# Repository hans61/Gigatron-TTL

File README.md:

# Gigatron-TTL - extensions and components

## In Circuit EPROM emulator and debugger
my assembly experiences with the project from  gesari (Jesus Arias)

https://github.com/hans61/Gigatron-TTL/tree/main/InCircuitEPROMemulator

## Pluggy-Reloaded
A Pluggy Reloaded with the Arduino Nano Every.

## FreeCAD
My useful things for the 3d printer.

## 8Bit-audio
Attempt of audio output with a DAC TLC7524 at the external extension of lb3361.

## Video-Repeater
A pcb for the video repeater from Axelb.

## sound card
Sound card with sn76489 (in progress)

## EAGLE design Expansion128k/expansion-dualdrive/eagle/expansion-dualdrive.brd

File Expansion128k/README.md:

# Gigatron Extension 128k+

The 128k+ extension provides 128 kbyte RAM and an SPI interface for the Gigatron.
The first draft was discussed here: https://forum.gigatron.io/viewtopic.php?f=4&t=64

Another extension is lb3361's expansion-retro https://github.com/lb3361/gigatron-lb/tree/main/extension-retro.
It uses two GAL and extends the original with additional I/O functions. The GAL also allows changes to the function through GAL programming.

For all those who don't want GALs and for the new "dev128k7.rom" from lb3361 I made a new PCB from Marcel's original. The extension includes all the latest changes and pin header for two SD card breakout.

In the end there were two PCBs because an old problem reappeared while testing the first one. DANGER! the original circuit does not work with two SD cards and the current ROMs.
This is partly due to the SD cards, which only behave like SPI devices after they have been switched to this mode. The second problem is the SD breakout boards used, which permanently put the MISO signal on the output, independent of /CS. In the original circuit, the MISO signals are separated by the hardware, but they are combined again in the ROM
("anda(0b00001111) #28+i*12 This is why R1 as pull-DOWN is simpler").

One way to solve the problem is to modify the breakout, which requires some skill.

The second possibility is to solve it with hardware. I did that with the second PCB. I borrowed two gates from the 74125 for the solution. This reduces the available SPI on this PCB from 4 to 2.

I built and tested both PCBs. They work as expected.

## original

## dualdrive modify

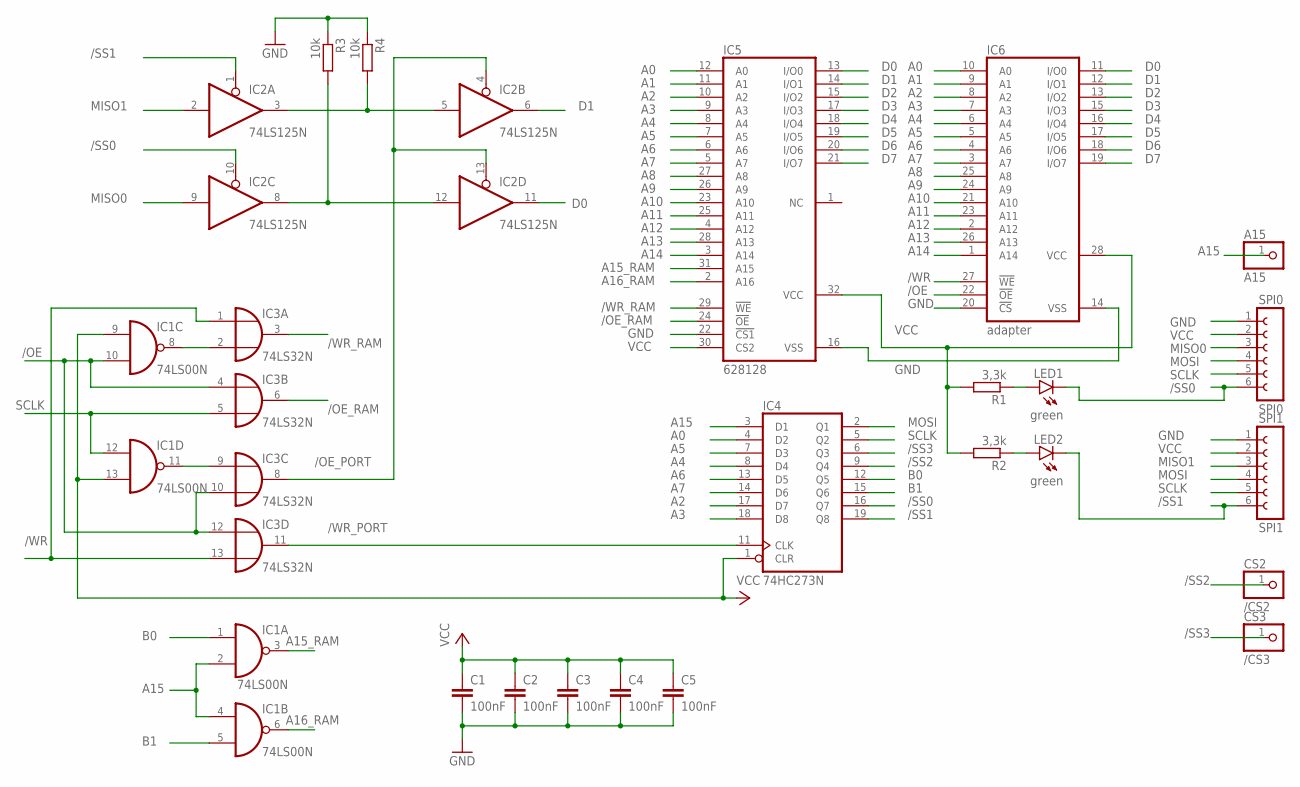
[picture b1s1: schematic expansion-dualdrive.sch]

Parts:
A15: A15; 1X01
C1, C2, C3, C4, C5: 100nF; C050-024X044
CS2: /CS2; 1X01
CS3: /CS3; 1X01
IC1: 74LS00N; DIL14
IC2: 74LS125N; DIL14
IC3: 74LS32N; DIL14
IC4: 74HC273N; DIL20
IC5: 628128; DIL32
IC6: adapter; DIL28-6
LED1, LED2: green; LED3MM
R1, R2: 3,3k; 0207/10
R3, R4: 10k; 0207/10
SPI0: SPI0; FE06
SPI1: SPI1; FE06

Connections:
/OE: IC1.10 (I1), IC3.4 (I0), IC3.10 (I1), IC3.12 (I0), IC6.22 (!OE)
/OE_PORT: IC2.4 (OE), IC2.13 (OE), IC3.8 (O)
/OE_RAM: IC3.6 (O), IC5.24 (!OE)
/SS0: IC2.10 (OE), IC4.16 (Q7), LED1.K (C), SPI0.6
/SS1: IC2.1 (OE), IC4.19 (Q8), LED2.K (C), SPI1.6
/SS2: CS2.1, IC4.9 (Q4)
/SS3: CS3.1, IC4.6 (Q3)
/WR: IC3.1 (I0), IC3.13 (I1), IC6.27 (!WE)
/WR_PORT: IC3.11 (O), IC4.11 (CLK)
/WR_RAM: IC3.3 (O), IC5.29 (!WE)
A0: IC4.4 (D2), IC5.12 (A0), IC6.10 (A0)
A1: IC5.11 (A1), IC6.9 (A1)
A2: IC4.17 (D7), IC5.10 (A2), IC6.8 (A2)
A3: IC4.18 (D8), IC5.9 (A3), IC6.7 (A3)
A4: IC4.8 (D4), IC5.8 (A4), IC6.6 (A4)
A5: IC4.7 (D3), IC5.7 (A5), IC6.5 (A5)
A6: IC4.13 (D5), IC5.6 (A6), IC6.4 (A6)
A7: IC4.14 (D6), IC5.5 (A7), IC6.3 (A7)
A8: IC5.27 (A8), IC6.25 (A8)
A9: IC5.26 (A9), IC6.24 (A9)
A10: IC5.23 (A10), IC6.21 (A10)
A11: IC5.25 (A11), IC6.23 (A11)
A12: IC5.4 (A12), IC6.2 (A12)
A13: IC5.28 (A13), IC6.26 (A13)
A14: IC5.3 (A14), IC6.1 (A14)
A15: A15.1, IC1.2 (I1), IC1.4 (I0), IC4.3 (D1)
A15_RAM: IC1.3 (O), IC5.31 (A15)
A16_RAM: IC1.6 (O), IC5.2 (A16)
B0: IC1.1 (I0), IC4.12 (Q5)
B1: IC1.5 (I1), IC4.15 (Q6)
D0: IC2.11 (O), IC5.13 (I/O0), IC6.11 (I/O0)
D1: IC2.6 (O), IC5.14 (I/O1), IC6.12 (I/O1)
D2: IC5.15 (I/O2), IC6.13 (I/O2)
D3: IC5.17 (I/O3), IC6.15 (I/O3)
D4: IC5.18 (I/O4), IC6.16 (I/O4)
D5: IC5.19 (I/O5), IC6.17 (I/O5)
D6: IC5.20 (I/O6), IC6.18 (I/O6)
D7: IC5.21 (I/O7), IC6.19 (I/O7)
GND: C1.2, C2.2, C3.2, C4.2, C5.2, IC1.7 (GND), IC2.7 (GND), IC3.7 (GND), IC4.10 (GND), IC5.16 (VSS), IC5.22 (!CS1), IC6.14 (VSS), IC6.20 (!CS), R3.1, R4.1, SPI0.1, SPI1.1
MI0: IC2.8 (O), IC2.12 (I), R3.2
MI1: IC2.3 (O), IC2.5 (I), R4.2
MISO0: IC2.9 (I), SPI0.3
MISO1: IC2.2 (I), SPI1.3
MOSI: IC4.2 (Q1), SPI0.4, SPI1.4
unnamed: IC1.8 (O), IC3.2 (I1)
unnamed: LED1.A, R1.1
unnamed: IC1.11 (O), IC3.9 (I0)
unnamed: LED2.A, R2.1
SCLK: IC1.12 (I0), IC3.5 (I1), IC4.5 (Q2), SPI0.5, SPI1.5
VCC: C1.1, C2.1, C3.1, C4.1, C5.1, IC1.9 (I0), IC1.13 (I1), IC1.14 (VCC), IC2.14 (VCC), IC3.14 (VCC), IC4.1 (CLR), IC4.20 (VCC), IC5.30 (CS2), IC5.32 (VCC), IC6.28 (VCC), R1.2, R2.2, SPI0.2, SPI1.2

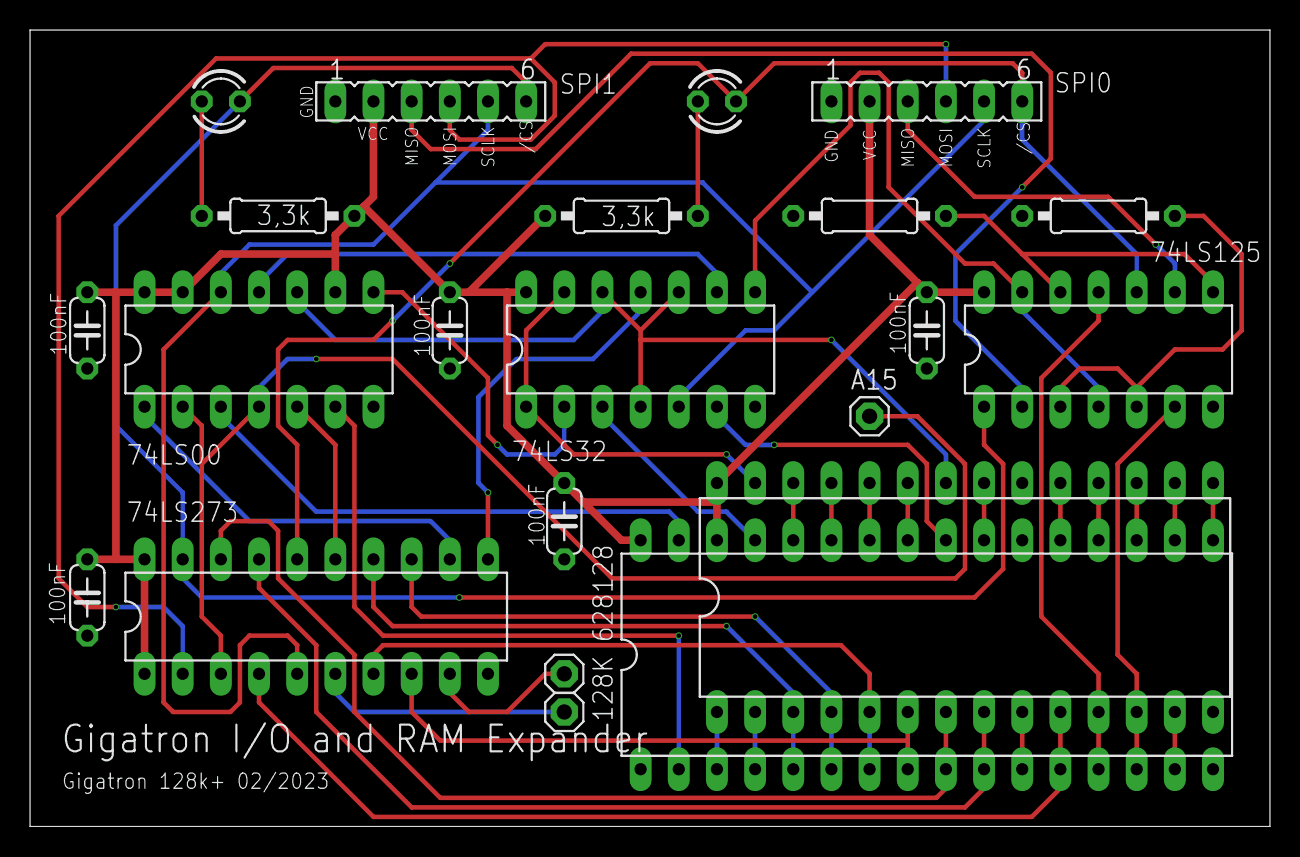
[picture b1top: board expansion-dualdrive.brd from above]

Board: 2 copper layers, 82.5 x 53.0 mm, 22 parts (0 on the bottom side), 50 nets.

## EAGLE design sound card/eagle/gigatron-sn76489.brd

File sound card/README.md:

# sound card with sn76489
I accidentally stumbled across the sound chip sn76489. Since it can only be controlled via outputs, it is well suited for the extension-retro of lb3361.
This is my attempt for a Gigatron sound card (Rev.3 still in work).

Unfortunately, I haven't had any success so far in producing a reasonable sound on the board. Now I have finally discovered the cause of the problem.
The SN76489 is available in two different pinouts. The difference is mirrored data pins.

| SN76489  Pin  | Pinout 1 | Pinout 2 |
|:-------:|:--------:|:--------:|
|    3    |    D0    |    D7    |
|    2    |    D1    |    D6    |
|    1    |    D2    |    D5    |
|   15    |    D3    |    D4    |
|   13    |    D4    |    D3    |
|   12    |    D5    |    D2    |
|   11    |    D6    |    D1    |
|   10    |    D7    |    D0    |

Pinout 1:
https://map.grauw.nl/resources/sound/texas_instruments_sn76489an.pdf

Pinout 2:
https://en.m.wikipedia.org/wiki/Texas_Instruments_SN76489

I solved the problem on the breadboard for now.

I'm still testing a small adapter board. When she leaves I will post it here.
I will also rework the PCB itself.

First tests (fast cell phone video):
https://www.youtube.com/watch?v=wv5x-WD0vzI

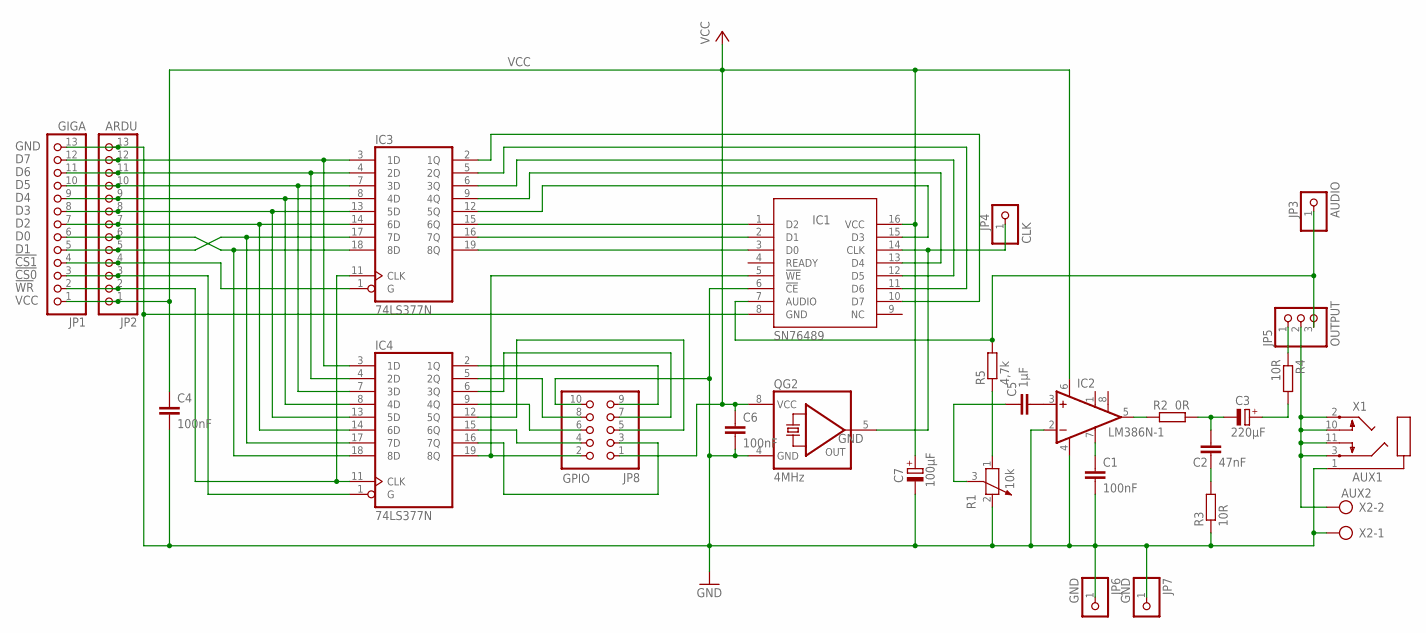
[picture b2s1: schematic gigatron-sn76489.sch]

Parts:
C1, C4, C6: 100nF; C050-025X075
C2: 47nF; C050-025X075
C3: 220µF; E2,5-7
C5: 1µF; C050-025X075
C7: 100µF; E2,5-7
IC1: SN76489; ALEX-PARTS_DIL16
IC2: LM386N-1; DIL08
IC3, IC4: 74LS377N; DIL20
JP1: GIGA; 1X13/90
JP2: ARDU; 1X13
JP3: AUDIO; 1X01
JP4: CLK; 1X01
JP5: OUTPUT; 1X03
JP6, JP7: GND; 1X01
JP8: GPIO; 2X05
QG2: 4MHz; DIL08S
R1: 10k; PT-10S
R2: 0R; 0207/10
R3, R4: 10R; 0207/10
R5: 4,7k; 0207/10
X1: AUX1; SJ1-352XN
X2: AUX2; AK500/2

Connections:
!CS0: IC4.1 (G), JP1.3, JP2.3
!CS1: IC3.1 (G), JP1.4, JP2.4
!SWR: IC1.5 (!WE), IC4.19 (8Q), JP8.2
!WR: IC3.11 (CLK), IC4.11 (CLK), JP1.2, JP2.2
AUXOUT: JP5.2, X1.2, X1.3, X1.10, X1.11, X2.2
CLK4MHZ: IC1.14 (CLK), JP4.1, QG2.5 (OUT)
D0: IC3.18 (8D), IC4.18 (8D), JP1.6, JP2.6
D1: IC3.17 (7D), IC4.17 (7D), JP1.5, JP2.5
D2: IC3.14 (6D), IC4.14 (6D), JP1.7, JP2.7
D3: IC3.13 (5D), IC4.13 (5D), JP1.8, JP2.8
D4: IC3.8 (4D), IC4.8 (4D), JP1.9, JP2.9
D5: IC3.7 (3D), IC4.7 (3D), JP1.10, JP2.10
D6: IC3.4 (2D), IC4.4 (2D), JP1.11, JP2.11
D7: IC3.3 (1D), IC4.3 (1D), JP1.12, JP2.12
GND: C1.2, C4.2, C6.2, C7.-, IC1.6 (!CE), IC1.8 (GND), IC2.2 (-IN), IC2.4 (GND), IC3.10 (GND), IC4.10 (GND), JP1.13, JP2.13, JP6.1, JP7.1, JP8.10, QG2.4 (GND), R1.2, R3.1, X1.1, X2.1
LM5: IC2.5 (OUT), R2.1
LM7: C1.1, IC2.7 (BYPASS)
unnamed: C3.+, R4.2
unnamed: JP5.1, R4.1
unnamed: C5.2, IC2.3 (+IN)
unnamed: C5.1, R1.3
unnamed: C2.2, R3.2
unnamed: R1.1, R5.1
unnamed: IC4.15 (6Q), JP8.4
unnamed: IC4.9 (4Q), JP8.6
unnamed: IC4.5 (2Q), JP8.8
unnamed: IC4.2 (1Q), JP8.9
unnamed: IC4.6 (3Q), JP8.7
unnamed: IC4.12 (5Q), JP8.5
unnamed: IC4.16 (7Q), JP8.3
R2C2C3: C2.1, C3.-, R2.2
SD0: IC1.3 (D0), IC3.19 (8Q)
SD1: IC1.2 (D1), IC3.16 (7Q)
SD2: IC1.1 (D2), IC3.15 (6Q)
SD3: IC1.15 (D3), IC3.12 (5Q)
SD4: IC1.13 (D4), IC3.9 (4Q)
SD5: IC1.12 (D5), IC3.6 (3Q)
SD6: IC1.11 (D6), IC3.5 (2Q)
SD7: IC1.10 (D7), IC3.2 (1Q)
SNOUT: IC1.7 (AUDIO), JP3.1, JP5.3, R5.2
VCC: C4.1, C6.1, C7.+, IC1.16 (VCC), IC2.6 (VS), IC3.20 (VCC), IC4.20 (VCC), JP1.1, JP2.1, JP8.1, QG2.8 (VCC)

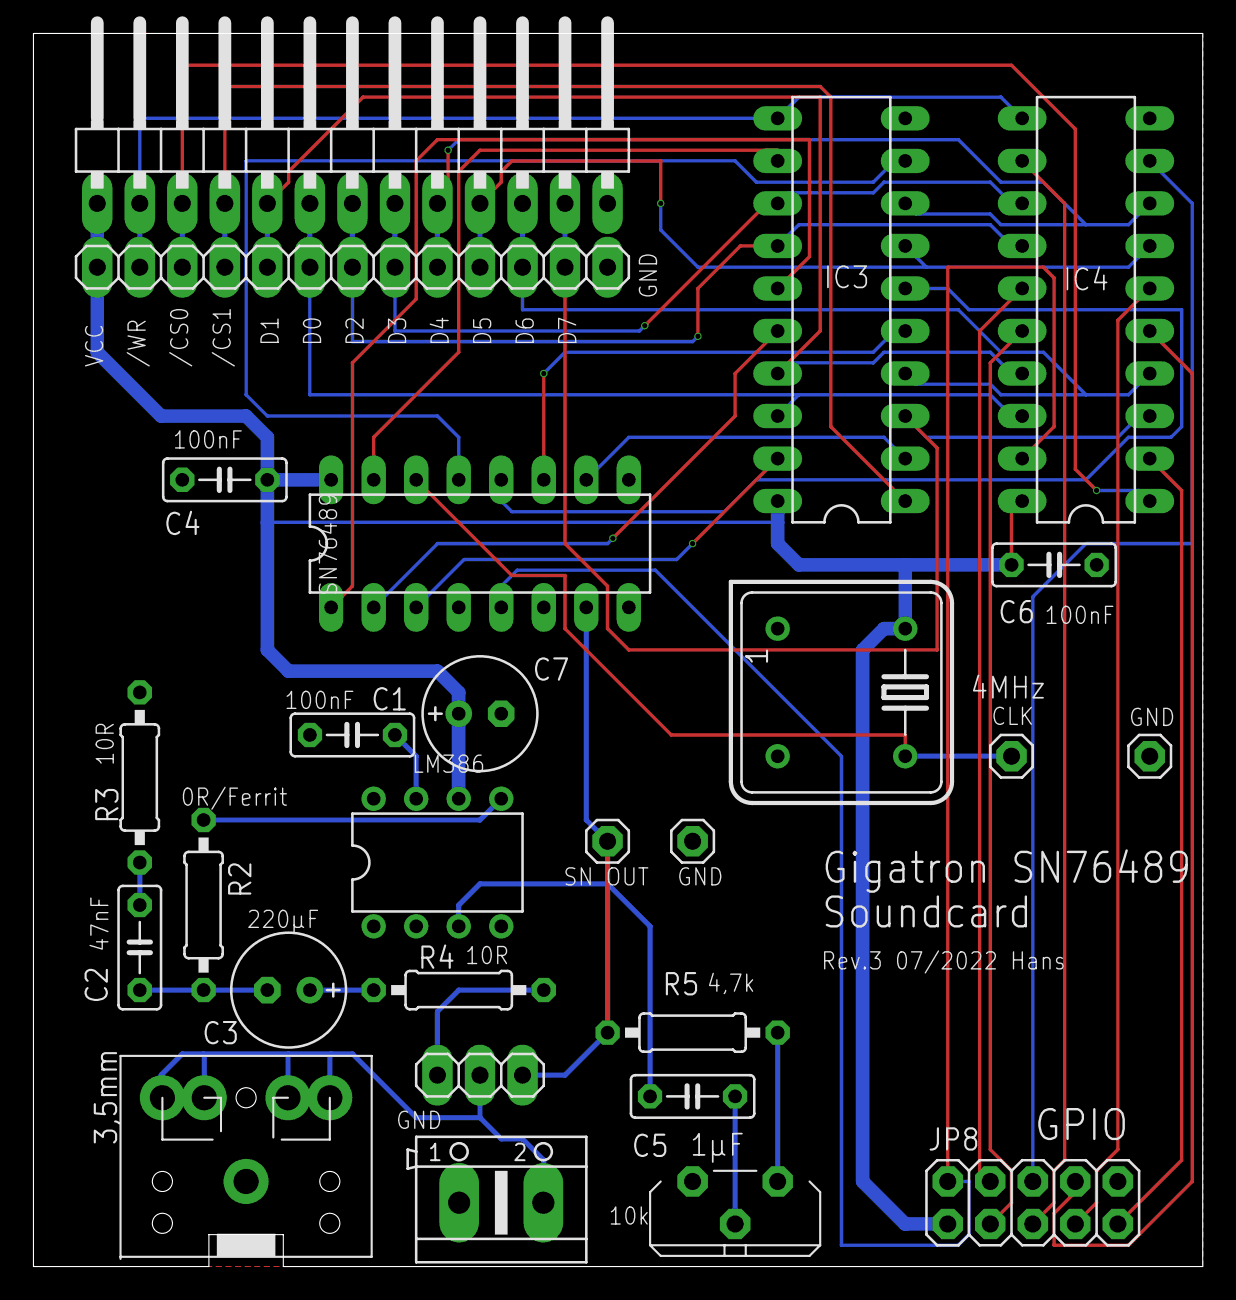
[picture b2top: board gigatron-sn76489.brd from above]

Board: 2 copper layers, 69.8 x 73.7 mm, 27 parts (0 on the bottom side), 41 nets.

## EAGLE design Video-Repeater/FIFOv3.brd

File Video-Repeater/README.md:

Video repeater for the Gigatron TTL computer Rev.3
==================================================
With the Gigatron TTL, a pixel consisting of 4 video lines is displayed in the VGA output. Since the video output is provided by software, it requires a large part of the computing power of the Gigatron. The video repeater records the first video line with a FIFO RAM and repeats it independently. The expansion has been tested and fits mechanically next to the "Expansion bus" (128k RAM + SPI) or the PCB from lb3361. The repeater adapts 74x377 (U37) from the mainboard.
It's the schematic from Axelb, thank you very much for the good work.

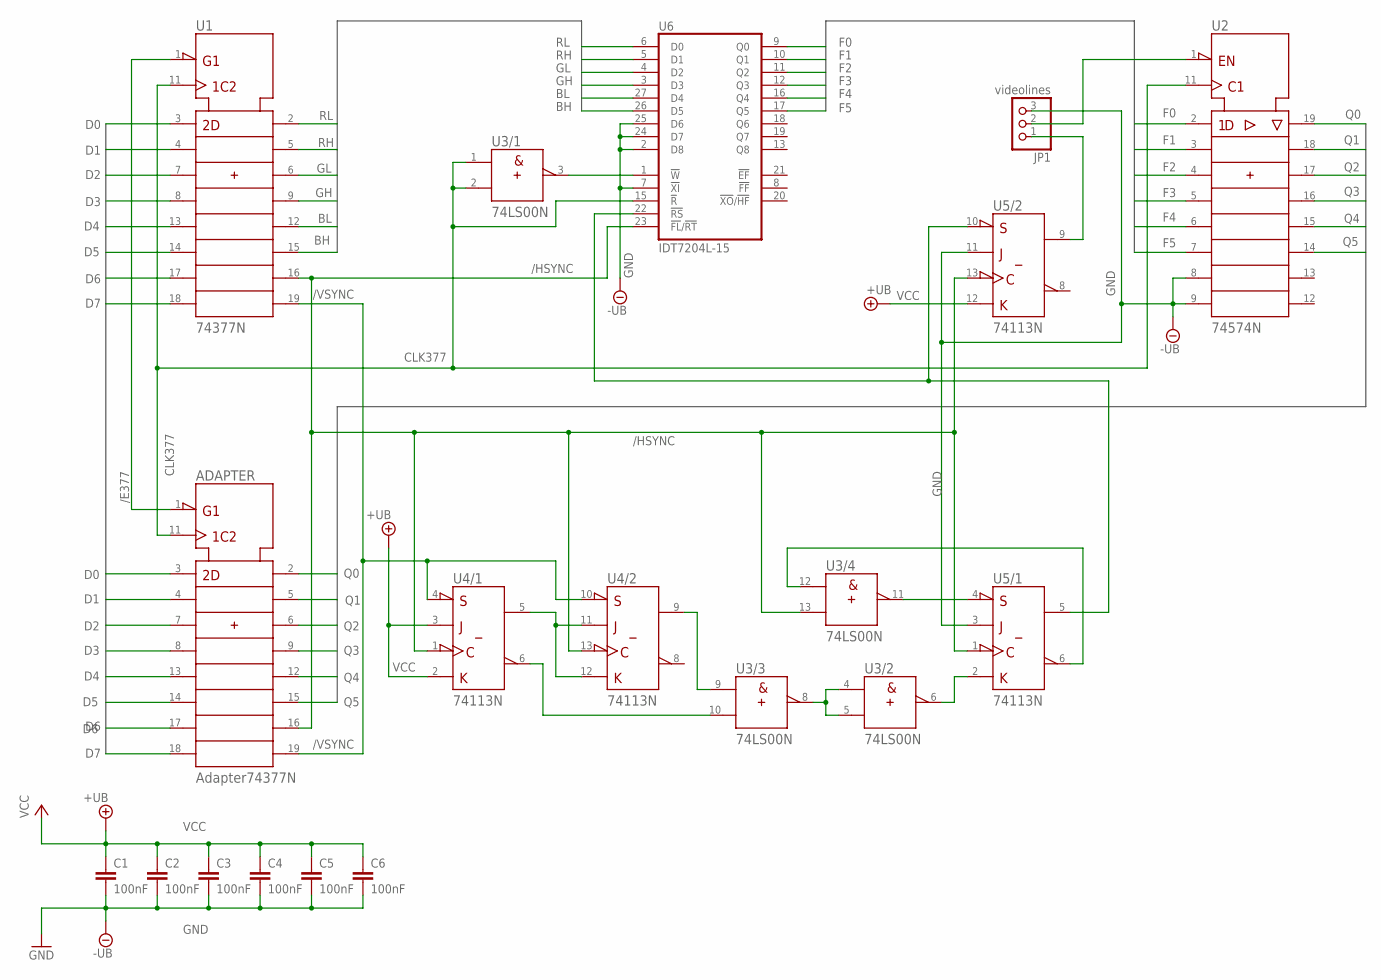
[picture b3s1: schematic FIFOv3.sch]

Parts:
ADAPTER: Adapter74377N; DIL20
C1, C2, C3, C4, C5, C6: 100nF; C5B2.5
JP1: videolines; 1X03
U1: 74377N; DIL20
U2: 74574N; DIL20
U3: 74LS00N; DIL14
U4, U5: 74113N; DIL14
U6: IDT7204L-15; DIL28-3

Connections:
/E377: ADAPTER.1 (!G), U1.1 (!G)
/HSYNC: ADAPTER.16 (7Q), U1.16 (7Q), U3.13 (B), U4.1 (CLK), U4.13 (CLK), U5.1 (CLK), U5.13 (CLK), U6.23 (!FL!/!RT)
/VSYNC: ADAPTER.19 (8Q), U1.19 (8Q), U4.4 (!PRE), U4.10 (!PRE)
BH: U1.15 (6Q), U6.26 (D5)
BL: U1.12 (5Q), U6.27 (D4)
CLK377: ADAPTER.11 (CLK), U1.11 (CLK), U2.11 (CLK), U3.1 (A), U3.2 (B), U6.15 (!R)
D0: ADAPTER.3 (1D), U1.3 (1D)
D1: ADAPTER.4 (2D), U1.4 (2D)
D2: ADAPTER.7 (3D), U1.7 (3D)
D3: ADAPTER.8 (4D), U1.8 (4D)
D4: ADAPTER.13 (5D), U1.13 (5D)
D5: ADAPTER.14 (6D), U1.14 (6D)
D6: ADAPTER.17 (7D), U1.17 (7D)
D7: ADAPTER.18 (8D), U1.18 (8D)
F0: U2.2 (1D), U6.9 (Q0)
F1: U2.3 (2D), U6.10 (Q1)
F2: U2.4 (3D), U6.11 (Q2)
F3: U2.5 (4D), U6.12 (Q3)
F4: U2.6 (5D), U6.16 (Q4)
F5: U2.7 (6D), U6.17 (Q5)
GH: U1.9 (4Q), U6.3 (D3)
GL: U1.6 (3Q), U6.4 (D2)
GND: ADAPTER.10 (-UB), C1.2, C2.2, C3.2, C4.2, C5.2, C6.2, JP1.3, U1.10 (-UB), U2.8 (7D), U2.9 (8D), U2.10 (-UB), U3.7 (-UB), U4.7 (-UB), U5.3 (J), U5.7 (-UB), U5.11 (J), U6.2 (D8), U6.7 (!XI), U6.14 (GND), U6.24 (D7), U6.25 (D6)
unnamed: U4.5 (Q), U4.11 (J), U4.12 (K)
unnamed: U3.3 (Y), U6.1 (!W)
unnamed: U3.10 (B), U4.6 (!Q)
unnamed: U3.9 (A), U4.9 (Q)
unnamed: U3.4 (A), U3.5 (B), U3.8 (Y)
unnamed: U3.6 (Y), U5.2 (K)
unnamed: U3.11 (Y), U5.4 (!PRE)
unnamed: U3.12 (A), U5.6 (!Q)
unnamed: JP1.1, U5.9 (Q)
unnamed: JP1.2, U2.1 (!OC)
unnamed: U5.5 (Q), U5.10 (!PRE), U6.22 (!RS)
Q0: ADAPTER.2 (1Q), U2.19 (1Q)
Q1: ADAPTER.5 (2Q), U2.18 (2Q)
Q2: ADAPTER.6 (3Q), U2.17 (3Q)
Q3: ADAPTER.9 (4Q), U2.16 (4Q)
Q4: ADAPTER.12 (5Q), U2.15 (5Q)
Q5: ADAPTER.15 (6Q), U2.14 (6Q)
RH: U1.5 (2Q), U6.5 (D1)
RL: U1.2 (1Q), U6.6 (D0)
VCC: ADAPTER.20 (+UB), C1.1, C2.1, C3.1, C4.1, C5.1, C6.1, U1.20 (+UB), U2.20 (+UB), U3.14 (+UB), U4.2 (K), U4.3 (J), U4.14 (+UB), U5.12 (K), U5.14 (+UB), U6.28 (VCC)

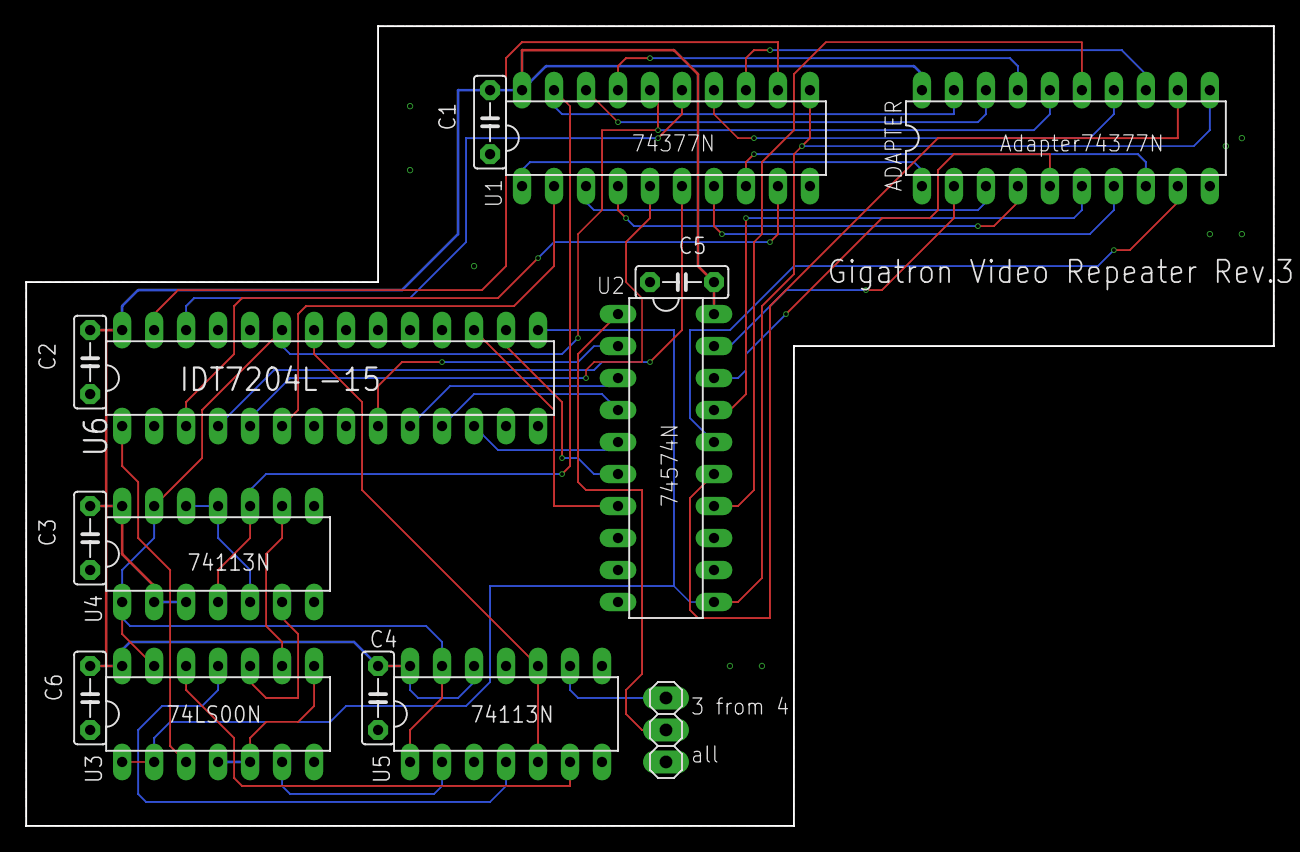
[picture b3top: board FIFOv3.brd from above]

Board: 2 copper layers, 99.1 x 63.5 mm, 14 parts (0 on the bottom side), 43 nets.

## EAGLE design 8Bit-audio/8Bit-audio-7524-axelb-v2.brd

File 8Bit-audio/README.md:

8 Bit Audo with the TLC7524 Rev. 2
==================================

It is the second draft that tries to avoid the mistakes of the first version. The connection to VREF (15) has been changed. The pin header was adapted to the PCB of lb3361. This means that a 1 to 1 cable can be used. Component footprints have been improved.
! This is just a draft.

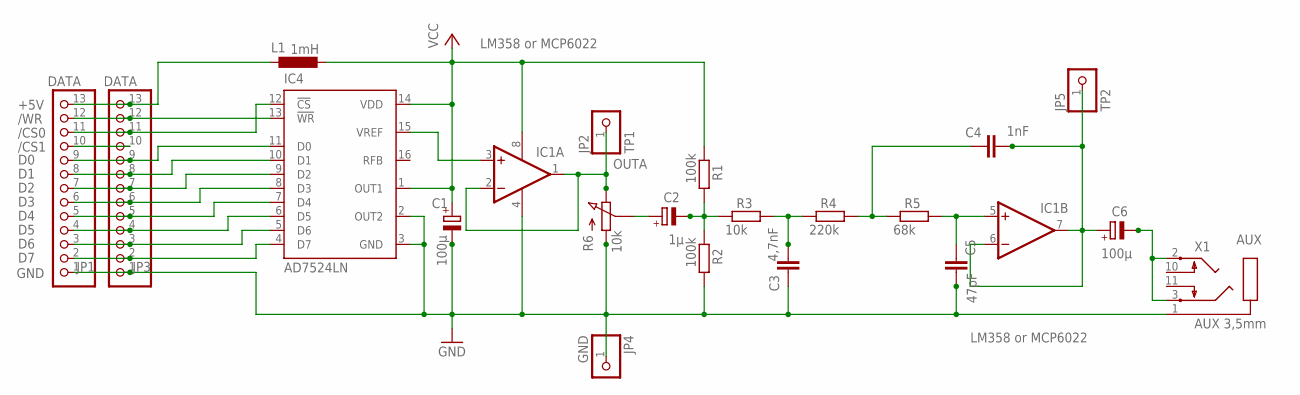
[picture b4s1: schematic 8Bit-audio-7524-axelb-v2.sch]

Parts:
C1, C6: 100µ; E2,5-7
C2: 1µ; E2,5-7
C3: 4,7nF; RCL_C025_050-055X075
C4: 1nF; RCL_C025_050-055X075
C5: 47pF; RCL_C025_050-055X075
IC1: LM358 or MCP6022; DIL08
IC4: AD7524LN; DIL16
JP1, JP3: DATA; 1X13
JP2: TP1; 1X01
JP4: GND; 1X01
JP5: TP2; 1X01
L1: 1mH; 0207/10
R1, R2: 100k; 0207/10
R3: 10k; 0207/10
R4: 220k; 0207/10
R5: 68k; 0207/10
R6: 10k; POT_3RP/1610N
X1: AUX 3,5mm; SJ1-352XN

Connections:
+5V: JP1.13, JP3.13, L1.1
/CS0: IC4.12 (!CS), JP1.11, JP3.11
/CS1: JP1.10, JP3.10
/WR: IC4.13 (!WR), JP1.12, JP3.12
AUX: C6.-, C6.-1 (-2), X1.2, X1.3
D0: IC4.11 (D0), JP1.9, JP3.9
D1: IC4.10 (D1), JP1.8, JP3.8
D2: IC4.9 (D2), JP1.7, JP3.7
D3: IC4.8 (D3), JP1.6, JP3.6
D4: IC4.7 (D4), JP1.5, JP3.5
D5: IC4.6 (D5), JP1.4, JP3.4
D6: IC4.5 (D6), JP1.3, JP3.3
D7: IC4.4 (D7), JP1.2, JP3.2
GND: C1.-, C1.-1 (-2), C3.1 (A1), C5.2 (B1), C5.3 (B2), IC1.4 (V-), IC4.2 (OUT2), IC4.3 (GND), JP1.1, JP3.1, JP4.1, R2.2, R6.A1, R6.A2, X1.1
unnamed: C2.-, C2.-1 (-2), R1.2, R2.1, R3.1
unnamed: C2.+, R6.M (S)
unnamed: C3.2 (B1), C3.3 (B2), R3.2, R4.1
unnamed: C4.1 (A1), R4.2, R5.1
unnamed: C5.1 (A1), IC1.5 (+IN), R5.2
OUTA: IC1.1 (OUT), IC1.2 (-IN), JP2.1, R6.E1, R6.E2
OUTB: C4.2 (B1), C4.3 (B2), C6.+, IC1.6 (-IN), IC1.7 (OUT), JP5.1
VCC: C1.+, IC1.8 (V+), IC4.1 (OUT1), IC4.14 (VDD), L1.2, R1.1
VREF: IC1.3 (+IN), IC4.15 (VREF)

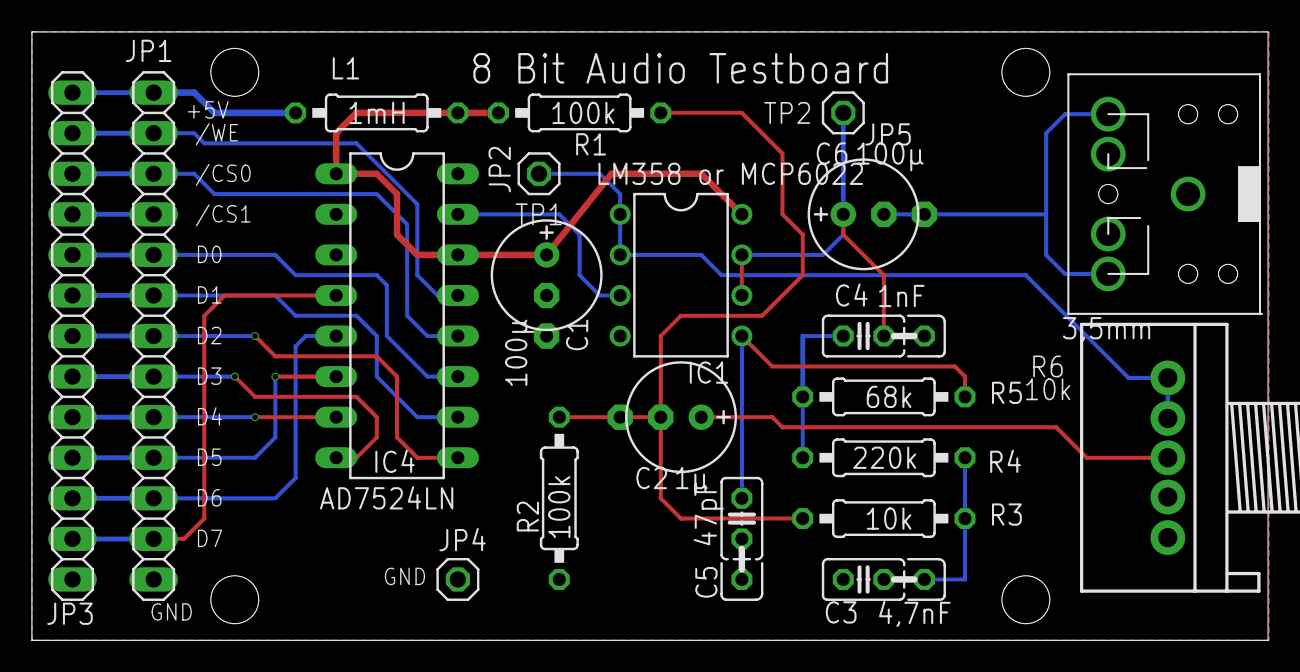
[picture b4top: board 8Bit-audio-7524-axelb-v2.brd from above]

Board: 2 copper layers, 77.4 x 38.1 mm, 21 parts (0 on the bottom side), 23 nets.

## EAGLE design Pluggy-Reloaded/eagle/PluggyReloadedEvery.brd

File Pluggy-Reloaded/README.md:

# Pluggy Reloaded
A new variant with the Arduino Nano Every with the new ATmega4809 CPU.
- 48KB Flash
- 6KB RAM
- 256B EEPROM

The reason it is at the moment better to get than the Pro Micro and in addition still more favorably (Reichelt approx. 10€)

I have also provided an I2C EEPROM, but have not made any software for it yet. I inserted and tested the board with the Arduino Nano Every 4809 in the existing software.

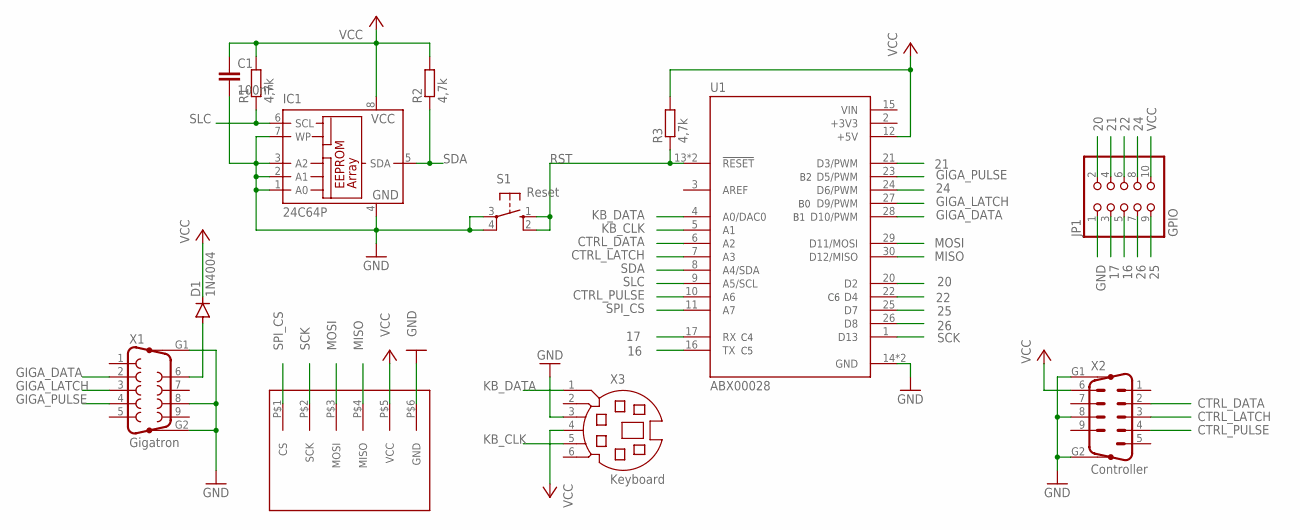
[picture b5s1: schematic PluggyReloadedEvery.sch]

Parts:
C1: 100nF; C050-024X044
D1: 1N4004; DO41-10
IC1: 24C64P; DIL8
JP1: GPIO; 2X05
R1, R2, R3: 4,7k; 0207/10
S1: Reset; B3F-10XX
U1: ABX00028; MODULE_ABX00028
U$1: BREAKOUT_SD
X1: Gigatron; F09HP
X2: Controller; M09HP
X3: Keyboard; MDIN06SS

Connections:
16: JP1.5, U1.16 (TX)
17: JP1.3, U1.17 (RX)
20: JP1.2, U1.20 (D2)
21: JP1.4, U1.21 (D3/PWM)
22: JP1.6, U1.22 (D4)
24: JP1.8, U1.24 (D6/PWM)
25: JP1.9, U1.25 (D7)
26: JP1.7, U1.26 (D8)
+3V3: U1.2 (+3V3)
CTRL_DATA: U1.6 (A2), X2.2
CTRL_LATCH: U1.7 (A3), X2.3
CTRL_PULSE: U1.10 (A6), X2.4
GIGA_DATA: U1.28 (D10/PWM), X1.2
GIGA_LATCH: U1.27 (D9/PWM), X1.3
GIGA_PULSE: U1.23 (D5/PWM), X1.4
GND: C1.2, IC1.1 (A0), IC1.2 (A1), IC1.3 (A2), IC1.4 (GND), IC1.7 (WP), JP1.1, S1.3, S1.4 (P1), U1.14 (GND), U1.19 (GND), U$1.P$6 (GND), X1.8, X1.G1, X1.G2, X2.8, X2.G1, X2.G2, X3.3
KB_CLK: U1.5 (A1), X3.5
KB_DATA: U1.4 (A0/DAC0), X3.1
MISO: U1.30 (D12/MISO), U$1.P$4 (MISO)
MOSI: U1.29 (D11/MOSI), U$1.P$3 (MOSI)
unnamed: D1.A, X1.6
RST: R3.1, S1.1 (S), S1.2 (S1), U1.13 (!RESET), U1.18 (!RESET)
SCK: U1.1 (D13), U$1.P$2 (SCK)
SDA: IC1.5 (SDA), R2.1, U1.8 (A4/SDA)
SLC: IC1.6 (SCL), R1.1, U1.9 (A5/SCL)
SPI_CS: U1.11 (A7), U$1.P$1 (CS)
VCC: C1.1, D1.C, IC1.8 (VCC), JP1.10, R1.2, R2.2, R3.2, U1.12 (+5V), U$1.P$5 (VCC), X2.6, X3.4
VIN: U1.15 (VIN)

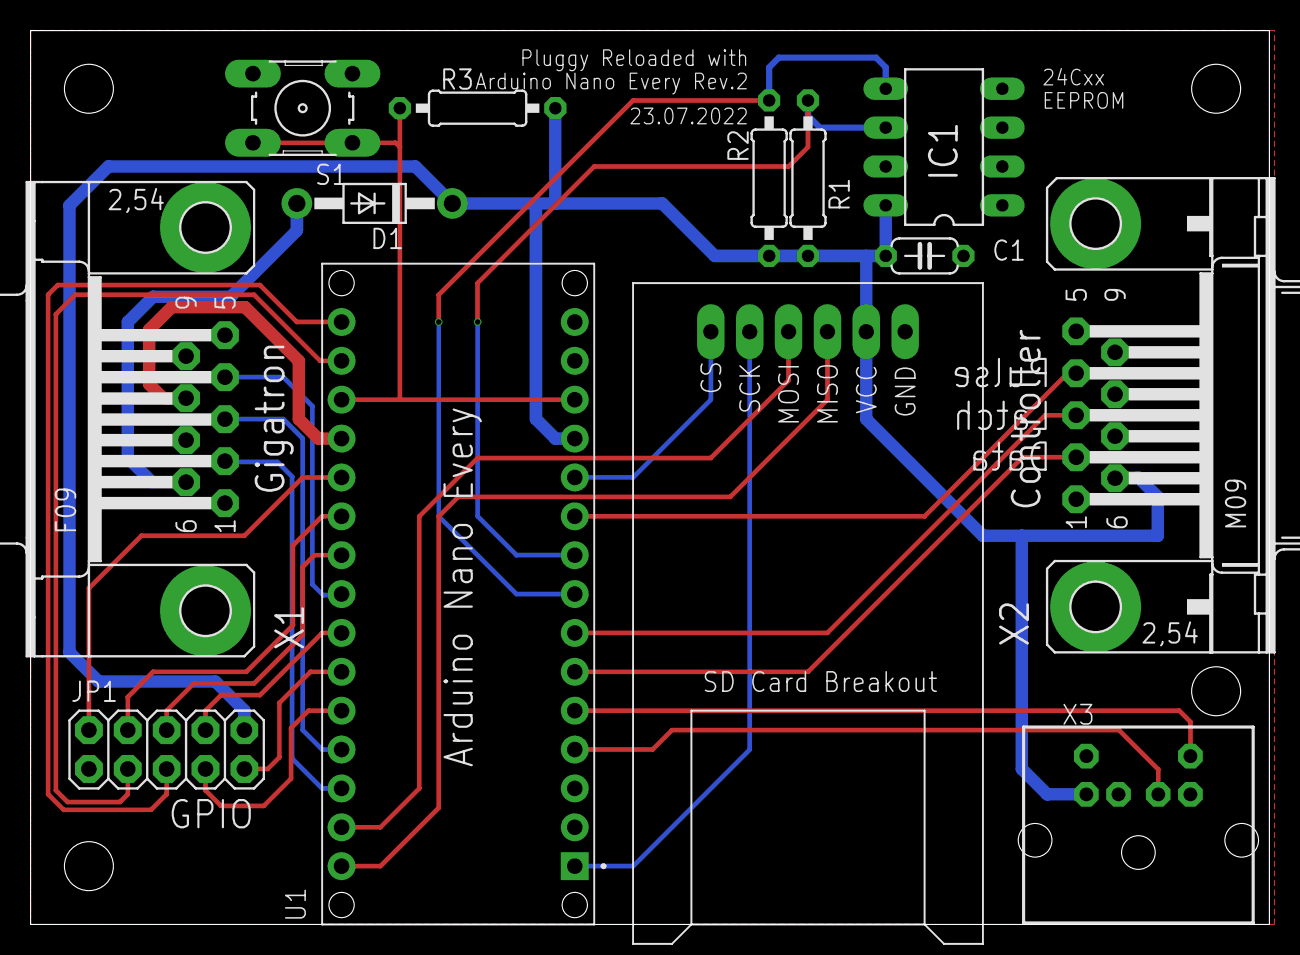
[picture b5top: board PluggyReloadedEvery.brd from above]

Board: 2 copper layers, 81.0 x 58.4 mm, 13 parts (0 on the bottom side), 26 nets.

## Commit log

2022-08-16 added eagle files revision 2
2022-08-16 added first picture
2022-08-16 added BabelFish source
2022-08-16 added Arduino Nano Every to BabelFish
2022-08-17 added freecad
2022-08-17 added audio with TLC7524
2022-08-17 added video repeater from Axelb
2022-08-17 added sound card
2023-02-19 added expansion 128k
2023-02-19 added picture
2023-05-04 Added the assembly of the In Circuit EPROM emulator and debugger.
2023-05-04 update In Circuit EPROM Emulator and Debugger
2023-05-07 picture soldering
2023-05-10 added picture test longfract.gt1
2023-05-21 More pictures added
2023-05-21 update FirstSteps
2023-05-24 added electrical connection with the Gigatron
2023-08-24 Updated Browser_SDCard_ROMv2 for more recent ROMs.
2024-03-25 Sound card tested successfully
2024-11-13 compiled hex files added
